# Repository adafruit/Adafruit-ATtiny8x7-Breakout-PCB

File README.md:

## Adafruit ATtiny8x7 Breakout PCB

<a href="http://www.adafruit.com/products/5233"><br/>
Click here to purchase one from the Adafruit shop</a>

PCB files for the Adafruit ATtiny8x7 Breakout. 

Format is EagleCAD schematic and board layout
* https://www.adafruit.com/product/5233

### Description

This breakout board is a "three in one" product:

1. The ATtiny817 is part of the 'next gen' of AVR microcontrollers, and now we have a cute development/breakout board for it, with just enough hardware to get the chip up and running.
2. It's also an Adafruit seesaw board. Adafruit seesaw is a near-universal converter framework which allows you to add and extend hardware support to any I2C-capable microcontroller or microcomputer. Instead of getting separate I2C GPIO expanders, ADCs, PWM drivers, etc, seesaw can be configured to give a wide range of capabilities.
3. Finally, with STEMMA QT connectors on it, you could use it as either an I2C controller or peripheral with plug-and play support.

We primarily designed this board for our own use: it's a mini dev board that lets us design with the ATtiny817 just like we did for the ATSAMD09. With the 2021 silicon shortage, we're adapting some of our SAMD09 designs to the ATTiny8xx series and wanted a quick minimal board to test code on.

Each breakout comes with the assembled and tested board, as well as some header strips. Each PCB is fairly minimal and contains:

* ATtiny817 8-bit microcontroller
    * 8KB flash, 512 bytes of RAM, 128 bytes of EEPROM
    * Internal oscillator can run up to 20MHz
    * Internal hardware multiplier
    * Can run from 2V to 5V power/logic (check the datasheet for max speed at desired power)
* 3.3V regulator - by default we run at the Vin voltage, which can be 5V, but there's a solder jumper on the bottom if you'd like to select 3V logic.
* Green power LED
* Red indicator LED
* Two STEMMA QT I2C connectors with 10K pullup resistors, connected to pins 10 and 11

This board comes pre-programmed with seesaw peripheral code that will let it act as an "I2C to something" converter, basically a little I2C-controlled friend to do all the timing-sensitive things many microcontrollers and microcomputers are not good at.

For example, using this breakout with the pre-burned seesaw firmware gives you

* 14 x GPIO with selectable pullup resistors
* 9 x 10-bit ADC inputs - pins 0, 1, 2, 3, 6, 7, 18, 19, 20
* 5 x 8-bit PWM outputs - pins 0, 1, 9, 12, 13
* 1 x NeoPixel output (up to 60 pixels)
* 1 x EEPROM with 127 byte of NVM memory (handy for storing small access tokens or MAC addresses) - last byte of EEPROM is used for I2C address selection
* 1 x Interrupt output that can be triggered by any of the accessories - pin 15
* 2 x I2C address selection pins - pins 16 and 17
* 1 x Activity LED on pin 5, tied active low

Of course you can configure or reprogram the chip to however you want to use it - we like using SpenceKonde's megaTinyCore which brings Arduino peripheral support to this series of chips. To program the chip you will need a 'UPDI' programmer, which you can make with a USB-to-Serial cable and a single 4.7K or 10K resistor.

Please note: The boards do not come with a bootloader. If you want to do development on seesaw (e.g. changing the configuration) you need a separate UPDI programming setup! The firmware we put on is available as this example sketch, compiled using the megaTinyCore. We don't provide any support for custom builds of seesaw - we think this is cool and useful for the Maker community!

### License

Adafruit invests time and resources providing this open source design, please support Adafruit and open-source hardware by purchasing products from [Adafruit](https://www.adafruit.com)!

Designed by Limor Fried/Ladyada for Adafruit Industries.

Creative Commons Attribution/Share-Alike, all text above must be included in any redistribution. 
See license.txt for additional details.

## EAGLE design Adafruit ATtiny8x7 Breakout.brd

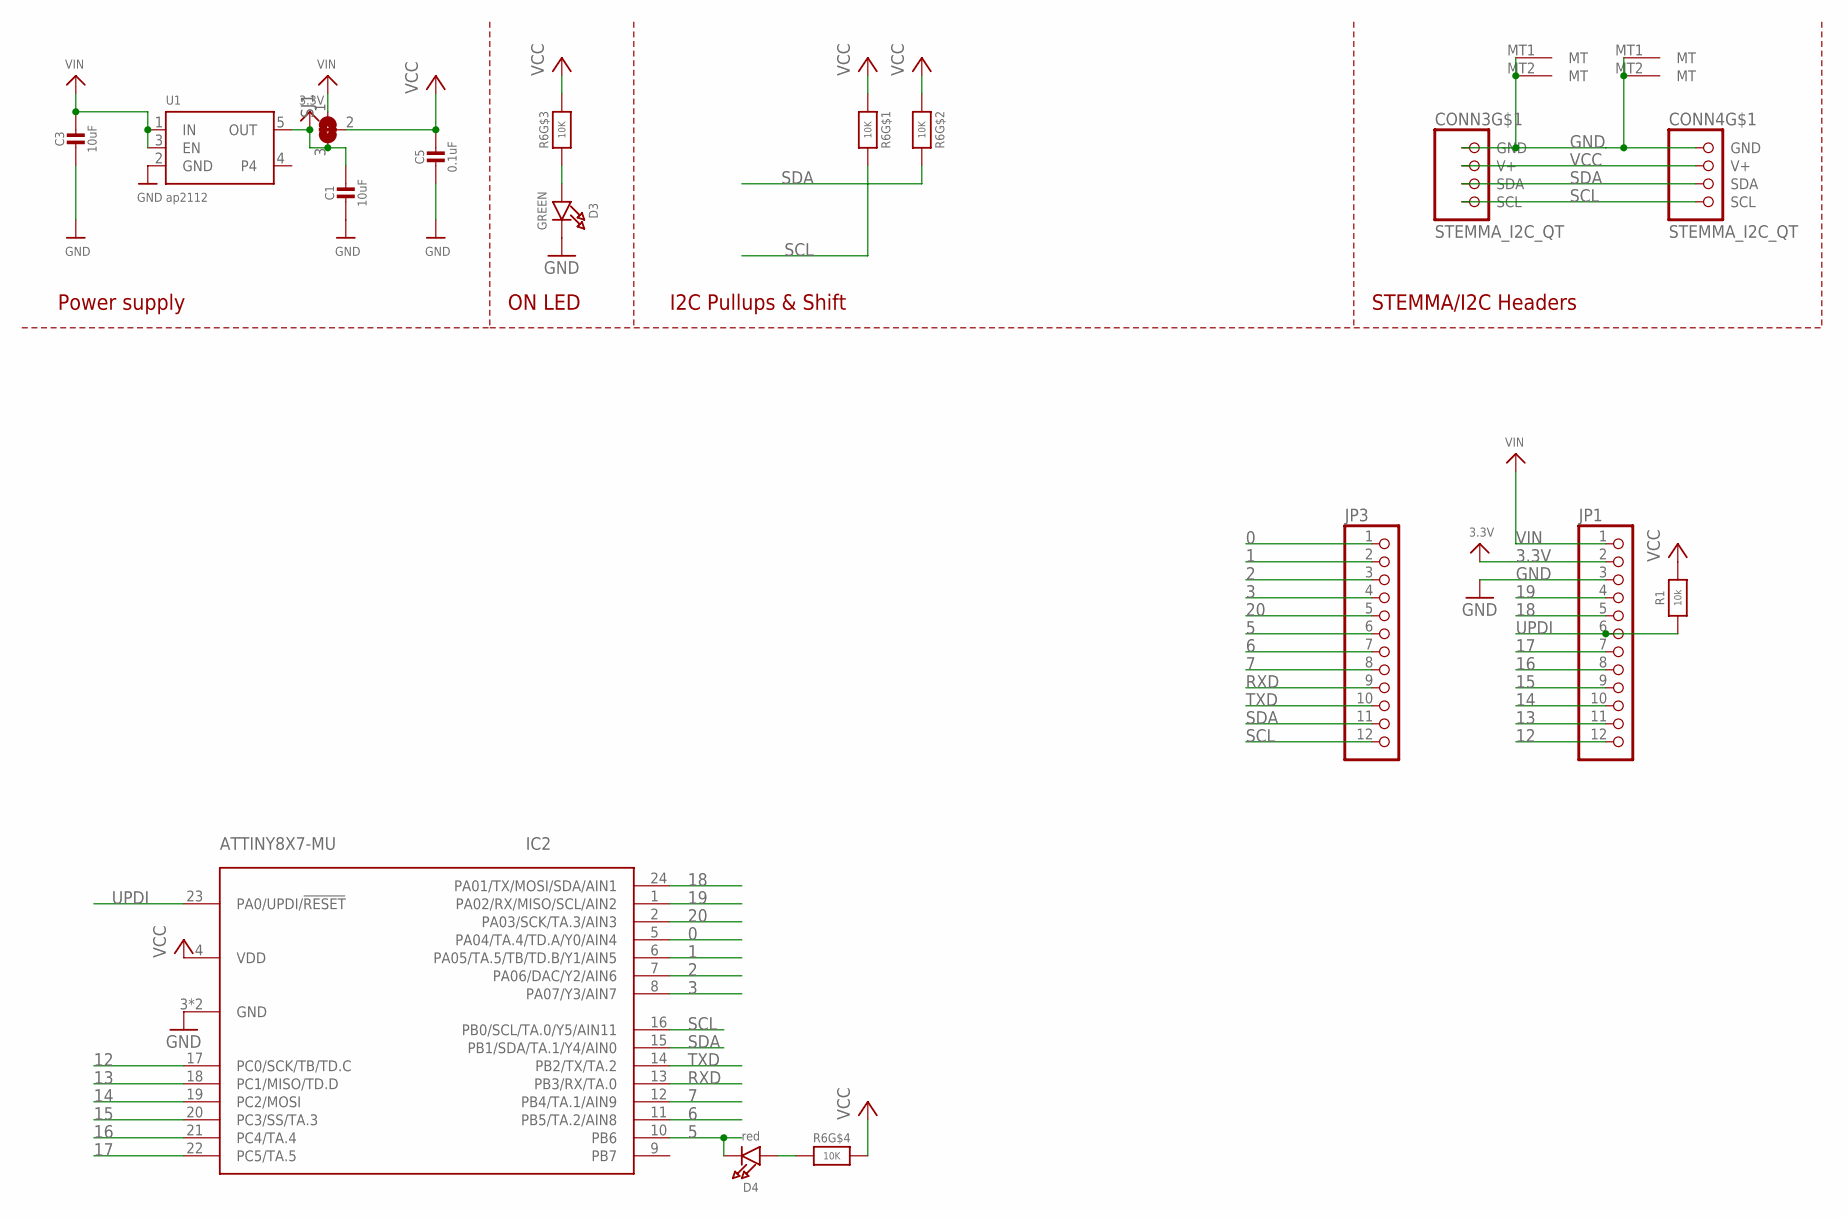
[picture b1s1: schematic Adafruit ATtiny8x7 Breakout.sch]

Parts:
C1: 10uF; 0805_10MGAP
C3: 10uF; 0805-NO
C5: 0.1uF; 0603-NO
CONN3, CONN4: STEMMA_I2C_QT; JST_SH4
D3: GREEN; CHIPLED_0603_NOOUTLINE
D4: red; CHIPLED_0603_NOOUTLINE
IC2: ATTINY8X7-MU; QFN24_4MM
JP1, JP3: HEADER-1X1276MIL; 1X12_ROUND_76MIL
R1: 10k; 0603-NO
R6: 10K; RESPACK_4X0603
SJ1: SOLDERJUMPER_2WAY; SOLDERJUMPER_2WAY_OPEN_NOPASTE
U1: ap2112; SOT23-5

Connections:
0: IC2.5 (PA04/TA.4/TD.A/Y0/AIN4), JP3.1
1: IC2.6 (PA05/TA.5/TB/TD.B/Y1/AIN5), JP3.2
2: IC2.7 (PA06/DAC/Y2/AIN6), JP3.3
3: IC2.8 (PA07/Y3/AIN7), JP3.4
3.3V: C1.1, JP1.2, SJ1.3, U1.5 (OUT)
5: D4.C, IC2.10 (PB6), JP3.6
6: IC2.11 (PB5/TA.2/AIN8), JP3.7
7: IC2.12 (PB4/TA.1/AIN9), JP3.8
12: IC2.17 (PC0/SCK/TB/TD.C), JP1.12
13: IC2.18 (PC1/MISO/TD.D), JP1.11
14: IC2.19 (PC2/MOSI), JP1.10
15: IC2.20 (PC3/SS/TA.3), JP1.9
16: IC2.21 (PC4/TA.4), JP1.8
17: IC2.22 (PC5/TA.5), JP1.7
18: IC2.24 (PA01/TX/MOSI/SDA/AIN1), JP1.5
19: IC2.1 (PA02/RX/MISO/SCL/AIN2), JP1.4
20: IC2.2 (PA03/SCK/TA.3/AIN3), JP3.5
GND: C1.2, C3.2, C5.2, CONN3.1 (GND), CONN3.MT1 (MT), CONN3.MT2 (MT), CONN4.1 (GND), CONN4.MT1 (MT), CONN4.MT2 (MT), D3.C, IC2.3 (GND), IC2.THERM (GND), JP1.3, U1.2 (GND)
unnamed: D3.A, R6.3 (1)
unnamed: D4.A, R6.4 (1)
RXD: IC2.13 (PB3/RX/TA.0), JP3.9
SCL: CONN3.4 (SCL), CONN4.4 (SCL), IC2.16 (PB0/SCL/TA.0/Y5/AIN11), JP3.12, R6.8 (2)
SDA: CONN3.3 (SDA), CONN4.3 (SDA), IC2.15 (PB1/SDA/TA.1/Y4/AIN0), JP3.11, R6.7 (2)
TXD: IC2.14 (PB2/TX/TA.2), JP3.10
UPDI: IC2.23 (PA0/UPDI/!RESET), JP1.6, R1.1
VCC: C5.1, CONN3.2 (V+), CONN4.2 (V+), IC2.4 (VDD), R1.2, R6.1, R6.2 (1), R6.5 (2), R6.6 (2), SJ1.2
VIN: C3.1, JP1.1, SJ1.1, U1.1 (IN), U1.3 (EN)

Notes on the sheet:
I2C Pullups & Shift
STEMMA/I2C Headers
ON LED
Power supply

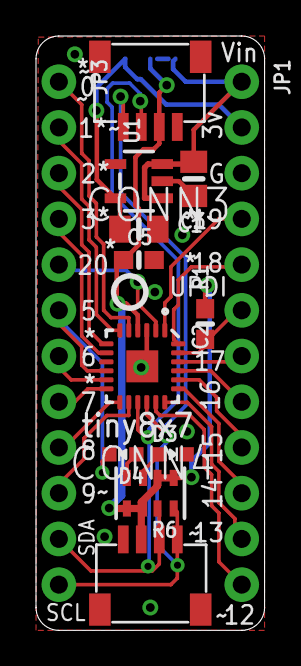
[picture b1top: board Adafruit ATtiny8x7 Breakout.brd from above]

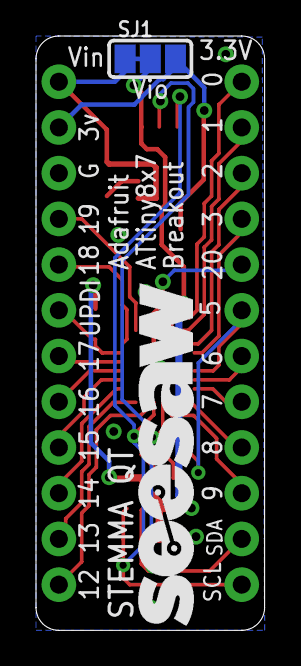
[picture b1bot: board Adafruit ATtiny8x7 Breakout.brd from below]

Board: 2 copper layers, 12.7 x 33.0 mm, 16 parts (2 on the bottom side), 27 nets.

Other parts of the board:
U$7: SEESAW_LOGO
U$12: PCBFEAT-REV-040

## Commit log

2021-10-14 Adding board files.

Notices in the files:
parts and their libraries:
microbuilder: This work is placed in the public domain, and may be freely used for commercial and non-commercial work with the following conditions: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
